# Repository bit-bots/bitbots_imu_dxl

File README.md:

# bitbots_imu_dxl

The Bitbots IMU DXL module is a Sensor module that can be connected to the Dynamixel Bus (RS485 or TTL).

[Documentation](http://doku.bit-bots.de/meta/manual/hardware/electronics/imu_dxl.html)

## Features

* 12 Bit 3 axis gyroscope and 3 axis accelerometer (MPU6500 sensor)
* 1000 Hz update rate
* configurable range (250-2000 deg/sec and 2-16g)
* configurable onboard complementary `filter <https://www.mdpi.com/1424-8220/15/8/19302>`_
* gyroscope and accelerometer calibration procedure
* direct reading of orientation as quaternion
* connection via the Dynamixel bus
* 3 RGB LEDs
* 3 Buttons

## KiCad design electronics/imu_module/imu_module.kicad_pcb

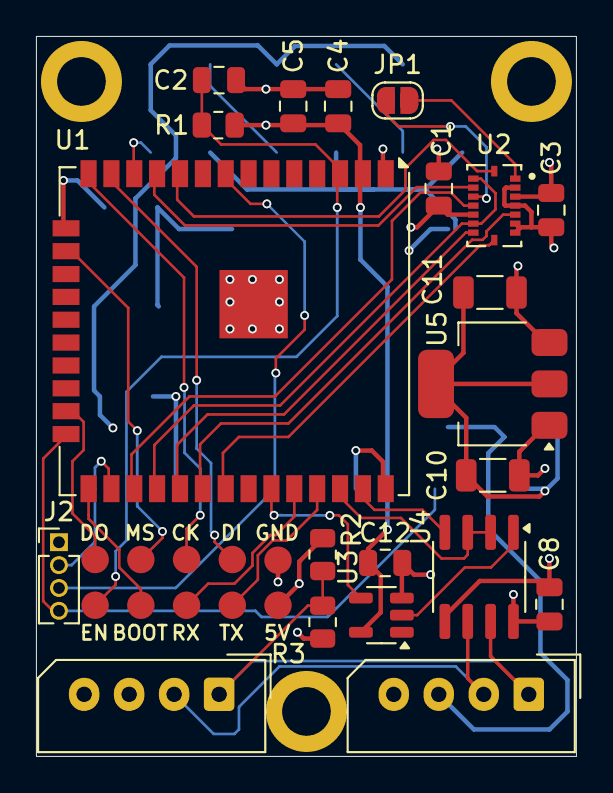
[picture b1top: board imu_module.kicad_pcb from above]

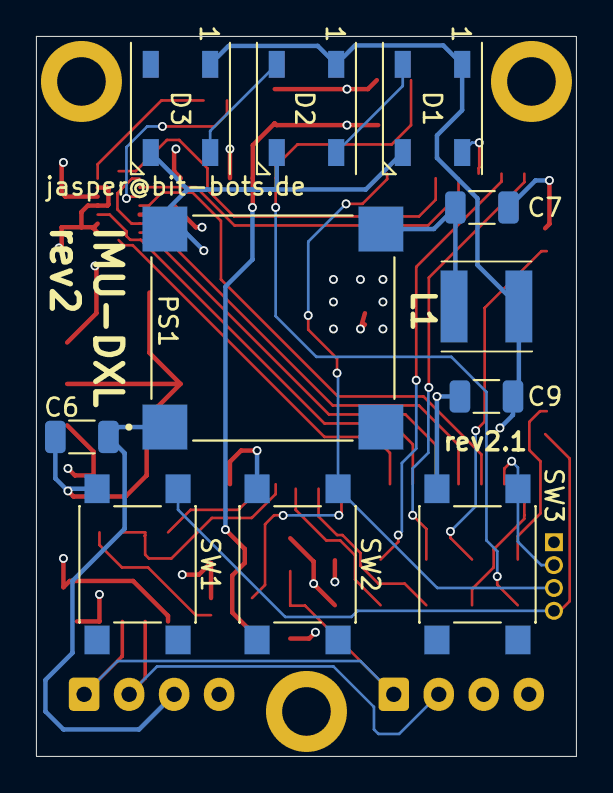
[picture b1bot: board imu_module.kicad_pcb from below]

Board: 4 copper layers, 30.0 x 40.0 mm, 36 parts (11 on the bottom side), 34 nets.

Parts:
C1, C2, C3, C4, C8, C12: 100n; C_0805_2012Metric
C5: 10u; C_0805_2012Metric
C6: 10u/50V; C_1206_3216Metric
C7, C9: 22u/16v; C_1206_3216Metric
C10, C11: 4.7u; C_1206_3216Metric
D1, D2, D3: WS2812B; LED_WS2812B_PLCC4_5.0x5.0mm_P3.2mm_marked
H1, H2, H3: MountingHole_Pad; MountingHole_2.7mm_M2.5_ISO14580_Pad
J1: PRGM+Debug; esp32_prgm_debug
J2: Conn_01x04_Pin; PinHeader_1x04_P1.27mm_Vertical
J3, J4: Conn_01x04; Molex_SPOX_5267-04A_1x04_P2.50mm_Vertical
JP1: SolderJumper_2_Open; SolderJumper-2_P1.3mm_Open_RoundedPad1.0x1.5mm
L1: VLS5045EX-220M; VLS5045EX330M
PS1: VXO7803-500-M; CONV_VXO7803-500-M
R1: 10K; R_0805_2012Metric
R2, R3: 4K7; R_0805_2012Metric
SW1, SW2, SW3: SW_Push; RND 210-00211
U1: ESP32-WROOM-32U; ESP32-WROOM-32UE
U2: BMI088
U3: SN74LV1T34DBV; SOT-23-5
U4: SP485; SOIC-8_3.9x4.9mm_P1.27mm
U5: AP2114HA-3.3TRG1; SOT-223-3_TabPin2

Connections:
+3V3: C1.1, C3.1, C4.1, C5.1, C11.1, C12.1, R1.1, U1.2 (VDD), U2.3 (VDD), U2.11 (VDDIO), U3.5 (VCC), U5.3 (OUT)
+5V: C8.1, C9.1, C10.1, D1.1 (VDD), D2.1 (VDD), D3.1 (VDD), J1.1, L1.2, R2.1, U4.8 (VCC), U5.1 (IN)
/5V_reg_out: C7.1, L1.1, PS1.3 (+VO)
DATA+: J3.2, J4.2, U4.6 (A)
DATA-: J3.1, J4.1, R2.2, R3.1, U4.7 (B)
GND: C1.2, C2.2, C3.2, C4.2, C5.2, C6.2, C7.2, C8.2, C9.2, C10.2, C11.2, C12.2, D1.3 (VSS), D2.3 (VSS), D3.3 (VSS), H1.1, H2.1, H3.1, J1.10, J2.1, J3.4, J4.4, PS1.2 (GND), R3.2, SW1.2, SW2.2, SW3.2, U1.1 (GND), U1.15 (GND), U1.38 (GND), U1.39 (GND), U2.2 (NC), U2.4 (GNDA), U2.6 (GNDIO), U2.7 (PS), U3.3 (GND), U4.5 (GND), U5.2 (GND)
JTAG_MTCK: J1.7, U1.16 (IO13)
JTAG_MTDI: J1.8, U1.14 (IO12)
JTAG_MTDO: J1.6, U1.23 (IO15)
JTAG_MTMS: J1.9, U1.13 (IO14)
LED: D1.4 (DIN), U1.12 (IO27)
unnamed: D1.2 (DOUT), D2.4 (DIN)
unnamed: D2.2 (DOUT), D3.4 (DIN)
SPI1_MISO: U1.28 (IO17), U2.10 (SDO2), U2.15 (SDO1)
SPI1_MOSI: U1.29 (IO5), U2.9 (SDA/SDI)
SPI1_SCK: U1.31 (IO19), U2.8 (SCL/SCK)
SPI_CS_ACCEL: U1.11 (IO26), U2.14 (CSB1)
SPI_CS_GYRO: U1.30 (IO18), U2.5 (CSB2)
SW1: J2.4, SW1.1, U1.24 (IO2)
SW2: J2.3, SW2.1, U1.8 (IO32)
SW3: J2.2, SW3.1, U1.26 (IO4)
TX_EN: U1.36 (IO22), U4.2 (~RE), U4.3 (DE)
U2_RX: U1.33 (IO21), U3.4 (Y)
U2_TX: U1.37 (IO23), U4.4 (DI)
VBUS: C6.1, J3.3, J4.3, PS1.1 (+VIN)
boot: J1.4, U1.25 (IO0)
en: C2.1, J1.5, R1.2, U1.3 (EN)
int1_accel: U1.10 (IO25), U2.16 (INT1)
int2_accel: JP1.1 (A), U2.1 (INT2)
int3_gyro: U1.27 (IO16), U2.12 (INT3)
int4_gyro: JP1.2 (B), U2.13 (INT4)
rs485_rx: U3.2 (A), U4.1 (RO)
rx_esp: J1.3, U1.34 (RXD0/IO3)
tx_esp: J1.2, U1.35 (TXD0/IO1)

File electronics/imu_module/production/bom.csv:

Designator,Footprint,Quantity,Value,LCSC Part #
"C1, C12, C2, C3, C4, C8",0805,6,100n,C49678
"C10, C11",1206,2,4.7u,C29823
C5,0805,1,10u,C15850
C6,1206,1,10u/50V,C13585
"C7, C9",1206,2,22u/16v,C12891
"D1, D2, D3",LED_WS2812B_PLCC4_5.0x5.0mm_P3.2mm_marked,3,WS2812B,
J1,esp32_prgm_debug,1,PRGM+Debug,
J2,PinHeader_1x04_P1.27mm_Vertical,1,Conn_01x04_Pin,
"J3, J4",Molex_SPOX_5267-04A_1x04_P2.50mm_Vertical,2,Conn_01x04,
L1,VLS5045EX330M,1,VLS5045EX-220M,
PS1,CONV_VXO7803-500-M,1,VXO7803-500-M,
R1,0805,1,10K,C17414
"R2, R3",0805,2,4K7,C17673
"SW1, SW2, SW3",RND 210-00211,3,SW_Push,
U1,ESP32-WROOM-32UE,1,ESP32-WROOM-32U,C3013937
U2,BMI088,1,BMI088,C194919
U3,SOT-23-5,1,SN74LV1T34DBV,C100024
U4,SOIC-8_3.9x4.9mm_P1.27mm,1,SP485,C6855
U5,SOT-223-3_TabPin2,1,AP2114HA-3.3TRG1,C460314

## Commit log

2020-06-26 add pcb, schematic and firmware
2020-08-10 started fast slave
2020-08-10 revert to "slow" slave
2020-08-11 working before fast_slave
2020-08-11 fast_slave working
2020-08-11 fix used constructor of fast_slave
2020-08-12 calibrate accel
2020-08-17 move read to loop, add accel calibration
2020-08-25 fix gyro order and quaternion order
2020-12-12 fix persistance of accel_gain after reboot
2021-01-19 bom and gerber
2021-10-29 fix bias estimation race condition
2021-12-02 kicad gitignore
2021-12-02 rm old files
2021-12-02 add new files
2021-12-02 add sym lib table
2021-12-02 add footprint lib table
2021-12-02 start pcb
2021-12-09 small fix
2023-06-16 firmware test version
2023-06-26 hacky
2024-01-04 update gitignore
2024-01-04 kicad project files
2024-02-02 Changed Pin configuration and variables
2024-02-06 "Split acc and gyro flag, currently running script"
2024-03-15 fixes for dxl communication
2024-03-15 Add imu test script
2024-03-15 Update Dynamixel2Arduino library
2024-03-15 Update test script
2024-03-17 working dxl with with esp32 idf
2024-03-17 port and led brightness
2024-03-17 working version with ~45us response latency
2024-03-17 rm fast slave
2024-03-17 cleanup
2024-03-18 pin versions of libraries and platform
2024-03-18 autoformat
2024-03-18 rm now untracked files
2024-03-18 rm output files
2024-03-18 rm gerber files
2024-03-18 rm old logo file
2024-03-18 rm lock file
2024-03-18 library updates
2024-03-18 rm production files as design is not quite finalized
2024-03-18 more cleanup and 3d models
2024-03-18 prep for production
2024-03-20 update submodule
2024-03-20 better support for bmi088 sensor
2024-03-20 fix setting of range and odr
2024-03-20 formatting
2024-03-20 rm comment
2024-03-21 new routing for buttons + leds on board
2024-06-24 production version and bom
2024-06-24 pin definitions and 3rd button
2024-07-10 update submodule for changes to axes
2024-07-10 fix time so that axes make sense
2024-07-10 final updates to revision
2024-07-15 first steps for configuring uart interrupt with dxl packets
2024-12-03 add schematic pdf
2025-02-14 Add first version of a rust dynamixel device
2025-02-14 Run format
2025-02-15 Add storage and multi core
2025-02-15 Add first version of config
2025-03-04 Current working state
2025-03-04 Add led driver
2025-03-06 State that is able to talk to ros_control
2025-03-06 Fix led order
2025-03-07 Correctly orient imu
2025-03-07 Report G
2025-03-07 Lets go faast
2025-03-07 Add version that works with 500Hz cycle
2025-03-07 Format
2025-03-07 Make clippy happy
2025-03-07 Restructure codebase
2025-03-07 Fix import
2025-03-08 Honor profiling flag for imu loop freq
2025-03-08 Add comments
2025-03-08 Use git version of imu driver
2025-03-08 Add button support
2025-03-15 Print ping after answer
2025-03-15 Use fork of dynamixel lib
2025-03-23 Bump versions
